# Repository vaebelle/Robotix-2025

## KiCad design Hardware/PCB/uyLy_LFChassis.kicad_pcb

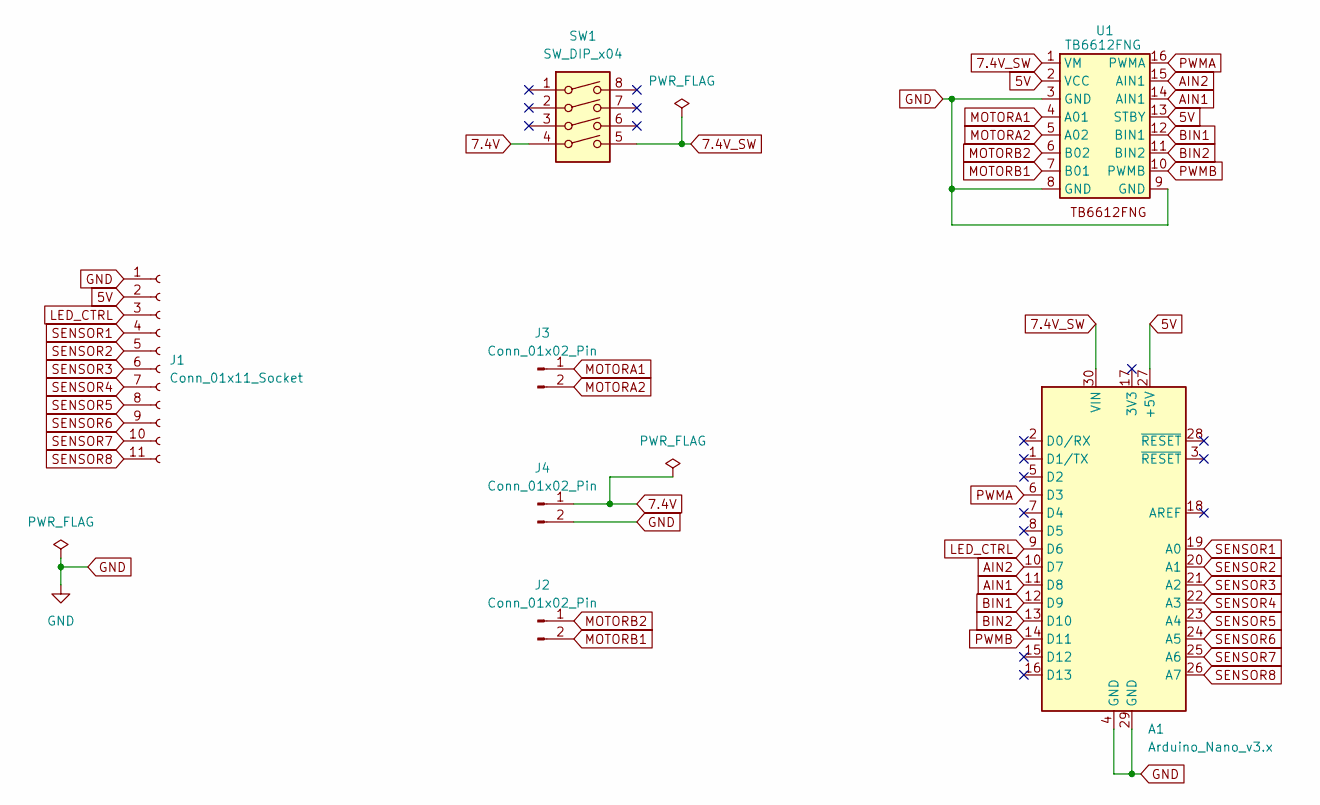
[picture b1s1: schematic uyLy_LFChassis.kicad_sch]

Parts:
A1: Arduino_Nano_v3.x; Arduino_Nano
J1: Conn_01x11_Socket; PinHeader_1x11_P2.54mm_Vertical
J2, J3: Conn_01x02_Pin; JST_XH_S2B-XH-A_1x02_P2.50mm_Horizontal
J4: Conn_01x02_Pin; JST_XH_B2B-XH-A_1x02_P2.50mm_Vertical
SW1: SW_DIP_x04; SW_DIP_SPSTx04_Slide_9.78x12.34mm_W7.62mm_P2.54mm
U1: TB6612FNG

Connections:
5V: A1.27 (+5V), J1.2, U1.2 (VCC), U1.13 (STBY)
7.4V: J4.1, SW1.4
7.4V_SW: A1.30 (VIN), SW1.5, U1.1 (VM)
AIN1: A1.11 (D8), U1.14 (AIN1)
AIN2: A1.10 (D7), U1.15 (AIN1)
BIN1: A1.12 (D9), U1.12 (BIN1)
BIN2: A1.13 (D10), U1.11 (BIN2)
GND: A1.4 (GND), A1.29 (GND), J1.1, J4.2, U1.3 (GND), U1.8 (GND), U1.9 (GND)
LED_CTRL: A1.9 (D6), J1.3
MOTORA1: J3.1, U1.4 (A01)
MOTORA2: J3.2, U1.5 (A02)
MOTORB1: J2.2, U1.7 (B01)
MOTORB2: J2.1, U1.6 (B02)
PWMA: A1.6 (D3), U1.16 (PWMA)
PWMB: A1.14 (D11), U1.10 (PWMB)
SENSOR1: A1.19 (A0), J1.4
SENSOR2: A1.20 (A1), J1.5
SENSOR3: A1.21 (A2), J1.6
SENSOR4: A1.22 (A3), J1.7
SENSOR5: A1.23 (A4), J1.8
SENSOR6: A1.24 (A5), J1.9
SENSOR7: A1.25 (A6), J1.10
SENSOR8: A1.26 (A7), J1.11

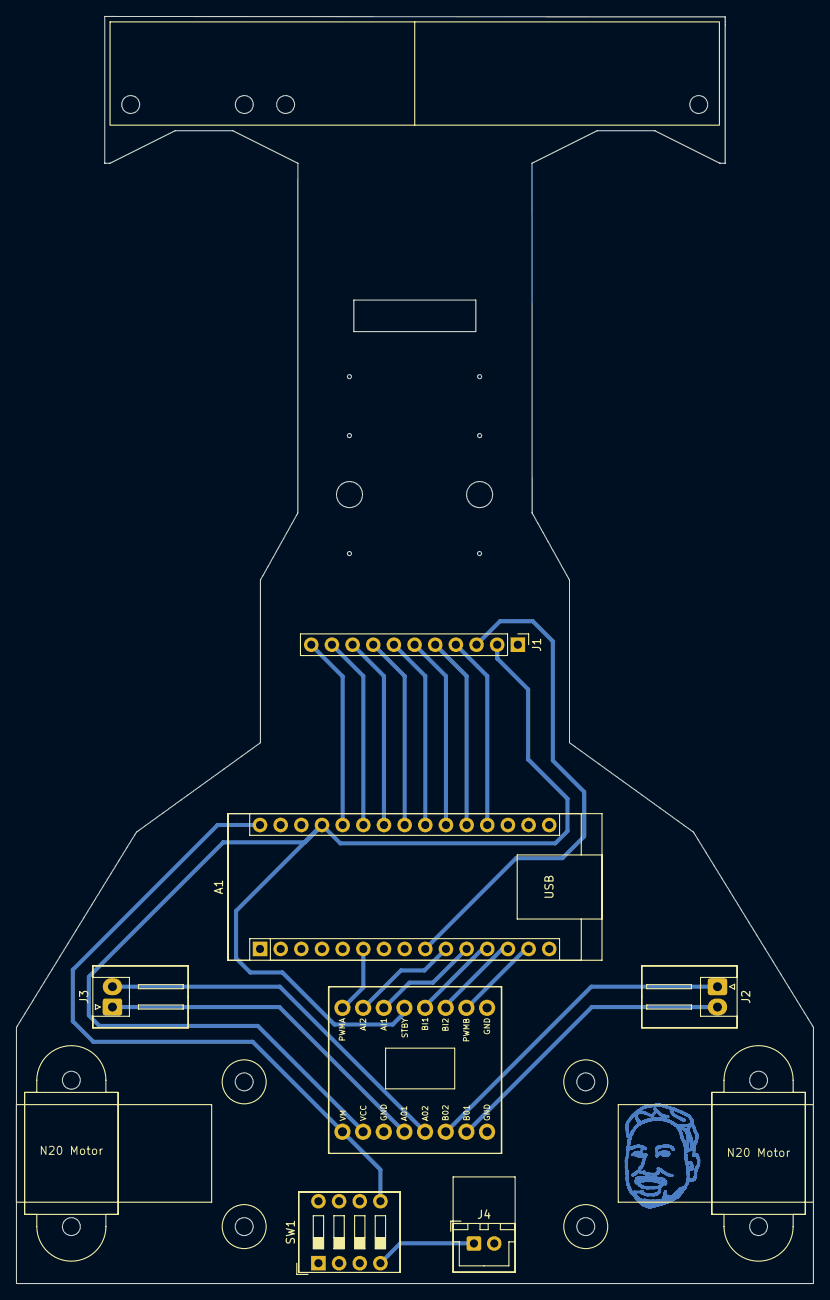
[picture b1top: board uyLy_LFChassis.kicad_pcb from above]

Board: 2 copper layers, 98.0 x 155.8 mm, 7 parts (0 on the bottom side), 23 nets.

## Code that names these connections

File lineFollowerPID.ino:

#include <QTRSensors.h>
#include <SparkFun_TB6612.h>

//QTR SENSOR PIN ASSIGNMENTS
#define SENSOR1 A0
#define SENSOR2 A1
#define SENSOR3 A2
#define SENSOR4 A3
#define SENSOR5 A4
#define SENSOR6 A5
#define SENSOR7 A6
#define SENSOR8 A7
#define LED_CTRL 6

//  PINS ASSIGNMENT
#define AIN1 8
#define AIN2 7
#define BIN1 9
#define BIN2 10
#define PWMA 3
#define PWMB 11

// motor
Motor rMotor = Motor (PWMA, AIN1, AIN2);
Motor lMotor = Motor (PWMB, BIN1, BIN2);


// PID values initialization
float kp = 0.305;
float ki = 0.00006;
float kd = 5

// sensor values initialization
const uint8_t sensorArray[8] = {SENSOR8, SENSOR7, SENSOR6, SENSOR5, SENSOR4, SENSOR3, SENSOR2, SENSOR1};
uint8_t sensorValActive[8];
uint8_t position;

//PID threshold values
int P, D, I, previousError, PIDValue, error, lsp, rsp, centerPosition, tempPosition;
centerPosition = 3500;

//Speed threshold values
int minSpeed, maxSpeed, baseSpeed; //255 full pwm range
minSpeed = -225;
maxSpeed = 255;
baseSpeed = 255;


void setup() {
  Serial.begin(9600);

  for (int i = 0; i <8; i++)
  {
    pinMode(sensorArray[i], INPUT);
  }
 
  qtr.setTypeAnalog();
  qtr.setSensorPins((const uint8_t[]){A7, A6, A5, A4, A3, A2, A1, A0}, 8);

  pinMode(LED_CTRL, OUTPUT);

}

void loop() {
  readSensorsActive(sensorValActive);
  
  /*
  NOTE:
  Sensor8 - left most  | sharp left
  Sensor7 -            | stronger than soft
  Sensor6 -            | soft left to the left
  Sensor5 - center     | center
  Sensor4 - center     | center
  Sensor3 -            | soft curve to the right
  Sensor2 -            | stronger than soft   
  Sensor1 - right most  | sharp right
  */

  //main pid calculations:
  // error = centerPosition - position;

  // P = error;
  // I = constrain(I + error, minSpeed, maxSpeed);
  // D = error - previousError;
  // previousError = error;

  // int motorSpeed = (Kp * P) + (Ki * I) + (Kd * D);

  // int lsp = constrain(baseSpeed + motorSpeed, minSpeed, maxSpeed);
  // int rsp = constrain(baseSpeed - motorSpeed, minSpeed, maxSpeed);

  // lmotor.drive(lsp);
  // rmotor.drive(rsp);

  void robot_control()
{
  position = qtr.readLineBlack(sensorValActive);

  if (position >= 3400)
  {
    motor1.drive(minSpeed);
    motor2.drive(maxSpeed);
  }
  else if (position <= 600)
  {
    motor1.drive(maxSpeed);
    motor2.drive(minSpeed);
  }
  else
  {
    error = centerPosition - position;

    P = error;
    I = constrain(I + error, minSpeed, maxSpeed);
    D = error - previousError;
    previousError = error;

    int motorSpeed = (Kp * P) + (Ki * I) + (Kd * D);

    int lsp = constrain(baseSpeed + motorSpeed, minSpeed, maxSpeed);
    int rsp = constrain(baseSpeed - motorSpeed, minSpeed, maxSpeed);

    motor1.drive(lsp);
    motor2.drive(rsp);
  }
}
}

void readSensorsActive (uint8_t* sensorValActive)
{
  digitalWrite(LED_CTRL, HIGH);
  delay(5);

  for (int i=0; i<8; i++)
  {
    sensorValActive[i] = analogRead(sensorArray[i]);
  }

  digitalWrite(LED_CTRL, LOW);
}

// void displayReadings (uint8_t* sensorReadings) {
//   uint8_t val_8 = sensorReadings[0];  
//   uint8_t val_7 = sensorReadings[1];          
//   uint8_t val_6 = sensorReadings[2];    
//   uint8_t val_5 = sensorReadings[3];       
//   uint8_t val_4 = sensorReadings[4];         
//   uint8_t val_3 = sensorReadings[5];      
//   uint8_t val_2 = sensorReadings[6];       
//   uint8_t val_1 = sensorReadings[7];

//   Serial.print("\t");
//   Serial.print("8: ");
//   Serial.print(val_8);
//   Serial.print("\t");
//   Serial.print("7: ");
//   Serial.print(val_7);
//   Serial.print("\t");
//   Serial.print("6: ");
//   Serial.print(val_6);
//   Serial.print("\t");
//   Serial.print("5: ");
//   Serial.print(val_5);
//   Serial.print("\t");
//   Serial.print("4: ");
//   Serial.print(val_4);
//   Serial.print("\t");
//   Serial.print("3: ");
//   Serial.print(val_3);
//   Serial.print("\t");
//   Serial.print("2: ");
//   Serial.print(val_2);
//   Serial.print("\t");
//   Serial.print("1: ");
//   Serial.print(val_1);

//   Serial.println();
// }

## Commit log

2025-03-11 Complete LF Code and Chassis
2025-03-11 Add custom footprints and symbols
2025-03-13 add: updated chassis
2025-03-15 update: pcb design
2025-03-16 Add relevant sensor reading functions
2025-03-16 Update Chassis PCB Design
2025-03-17 Finalize PCB Design and 3D Models
2025-03-18 guide: PID code file
2025-03-18 Add: PID code
2025-03-18 Add: position reader code
2025-03-18 Update sensor readings code
2025-03-24 Finalize Line Follower robot
2025-03-24 Create N20 Casterwheel footprint
2025-03-30 Finalize Hardware and Software
2025-03-30 Finalize 3D Parts
2025-03-31 Fix PCB Errors
